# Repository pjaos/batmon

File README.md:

# BATMON

## Overview
The batmon device connects to a Lithium ION battery (primarily aimed at Ebike batteries) and allows the user to
trade off the lifetime of the battery against the maximum single charge. The life of a lithium ION cell
is affected by many things, the maximum charge level of the cell, the temperature of the cell, the maximum
discharge of the cell etc. The batmon device allows the user to limit the maximum charge voltage of the cell
to reduce stresses on the battery chemistry.

For example if the maximum charge voltage of a Lithium ION cell is set to 4.1
volts per cell rather than the maximum of 4.2 volts per cell then the number of charge/discharge cycles
that the battery is capable of could be doubled. The trade off for this is that you will loose about 10 %
of the range on a single charge. If set to 4.0 volts per cell then the number of charge/discharge cycles
that the battery is capable of could be increased by four times. The trade off for this is that you will
loose about 25 % of the range on a single charge. The batmon device allows the user to set this trade off
by selecting the maximum charge voltage in five 0.05 volt steps from 4.2 to 4.0 volts.

The device also ensures that the battery is not charged when to cold or hot which also limits the batteries
lifetime. Charging at temperatures of 0°C or below can also be dangerous.

As stated previously this project is primarily aimed at improving the lifetime of Ebike batteries although the hardware could be used for other battery voltages with slight changes to the software. The device provides a WiFi connection. This can connect to your home WiFi network or run in stand alone (AP) mode. The [Yview App](https://github.com/pjaos/yview/tree/master/gui) can be used (Android phone/tablet or a Windows, Linux PC) to access the state of the battery (charge voltage/current etc) and configure the device settings.

## System Requirements
An initial set of requirements for the system is shown below.

* Charge the battery to a maximum voltage of between 4.0 and 4.2 Volts, configurable by the user.
* Display the charge voltage, current and power.
* Turn off charging if the battery temperature is too cold (<= 0°C).
* Turn off charging if the battery temperature is too hot (> 45°C)g.

## Hardware.
The hardware design uses an ESP32 CPU which provides the WiFi connectivity. An ADS1115 I2C 16 bit ADC device is used to measure the battery voltage, charge current and battery temperature. A Mosfet is used to turn off the battery charge once it reaches the configured charge voltage. The case for the module was 3D printed to provide a robust mount for the module inside the battery case.

")
")

Module installed into case in charger lead.

")

Module installed inside Ebike battery box.

")
")
")

## Software
The software that runs on the device is written in C and uses the [Mongoose OS](https://mongoose-os.com/).
It provides a web interface and integrates with the [YView](https://github.com/pjaos/yview) Iot archetecture.
The web interface is shown below.

The configuration page allow the user to trade off battery charge level against
the longevity of the battery pack via the 5 radio buttons at the top of the page.
 * 5 = max battery life but only charges the battery pack to 4 volts per cell.
 * 1 = min battery life but charges the battery pack to 4.2 volts per cell.

 The default is 3 with charges the battery pack to 4.1 volts per cell. This
 setting should approximately double the life (number of charge discharge cycles) when
 compared option 1. EBike battery chargers will normally charge a battery pack to this level. If option 5 is selected then the life of the battery should be approximately 4 times longer when compared to option 1.

The storage voltage checkbox can be selected if the user wishes to store the ebike for some time (E.G through the winter) and maximise the battery performance. This charges the battery to 3.7 volts.

The Device name can be set which sets the name that the device will appear as in the YView Iot network.

The group name can be set if the user wishes to partition the Iot network such that some users can see some devices.

The Enable syslog option is used for debugging and sends debugging information via the syslog protocol to the server running the YView Iot gateway process.

The save button will apply the configuration selected. The other buttons names are self explanatory.

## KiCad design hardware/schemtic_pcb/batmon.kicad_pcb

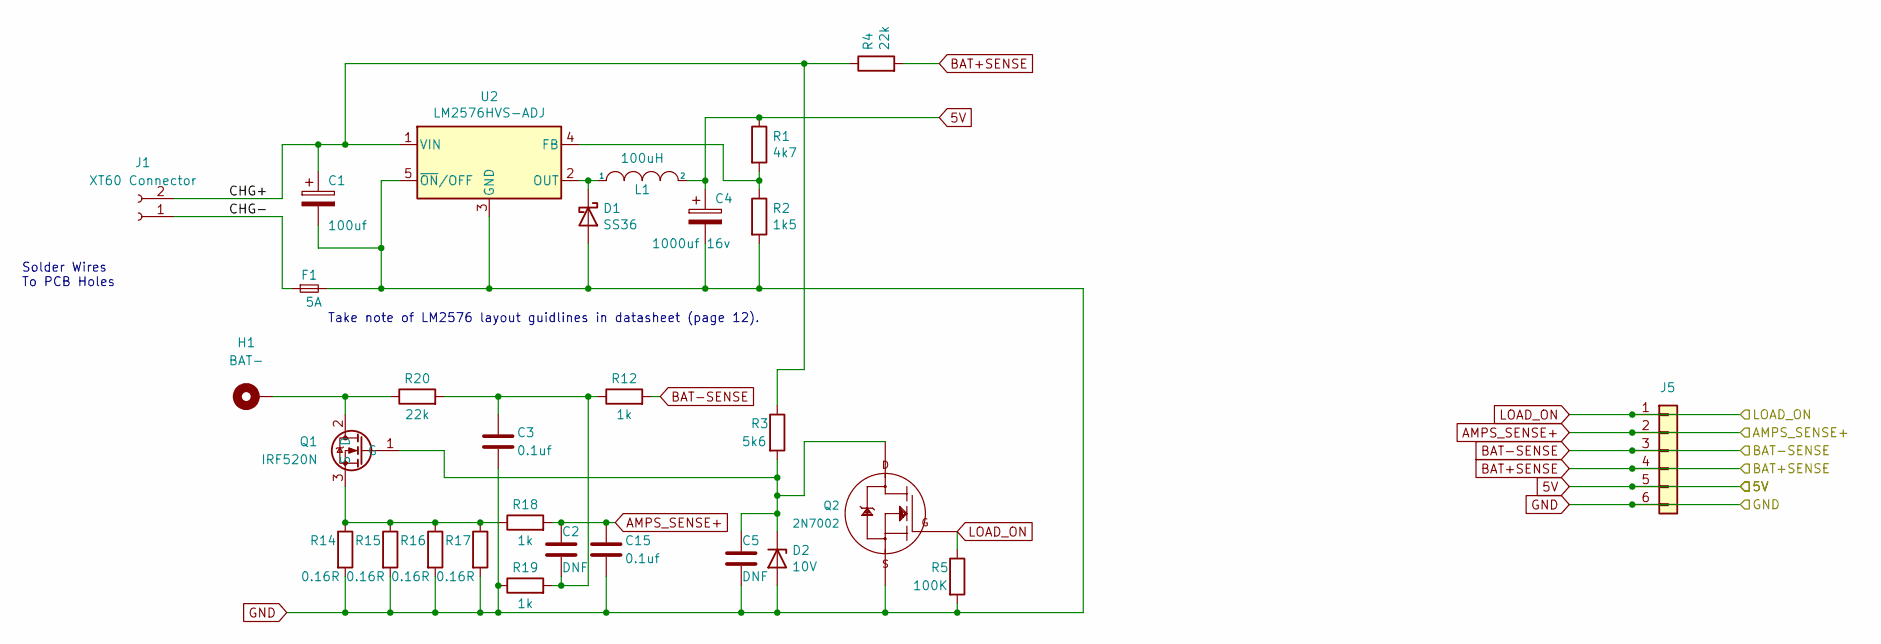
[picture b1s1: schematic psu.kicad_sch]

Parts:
C1: 100uf; CP_Radial_D10.0mm_P5.00mm
C2, C5: DNF; C_0603_1608Metric_Pad1.08x0.95mm_HandSolder
C3, C15: 0.1uf; C_0603_1608Metric_Pad1.08x0.95mm_HandSolder
C4: 1000uf 16v; CP_Radial_D10.0mm_P5.00mm
D1: SS36; D_MELF
D2: 10V; D_MELF
F1: 5A; Scherter_OMT125
H1: BAT-; MountingHole_3.2mm_M3_Pad
J1: XT60 Connector; AMASS_XT60-F_1x02_P7.20mm_Vertical
J5: Conn_01x06; PinHeader_1x06_P2.54mm_Vertical
L1: 100uH; Sumida_CDRH74
Q1: IRF520N; TO-220-3_Vertical
Q2: 2N7002; TSOT-23
R1: 4k7; R_0603_1608Metric_Pad0.98x0.95mm_HandSolder
R2: 1k5; R_0603_1608Metric_Pad0.98x0.95mm_HandSolder
R3: 5k6; R_0603_1608Metric_Pad0.98x0.95mm_HandSolder
R4, R20: 22k; R_0603_1608Metric_Pad0.98x0.95mm_HandSolder
R5: 100K; R_0603_1608Metric_Pad0.98x0.95mm_HandSolder
R12, R18, R19: 1k; R_0603_1608Metric_Pad0.98x0.95mm_HandSolder
R14, R15, R16, R17: 0.16R; R_1206_3216Metric_Pad1.30x1.75mm_HandSolder
U2: LM2576HVS-ADJ; TO-220-5_Vertical

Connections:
5V: C4.1, J5.5, L1.2, R1.1; also elsewhere on the board
/psu/CHG+: C1.1, J1.2, R3.1, R4.1, U2.1 (VIN)
/psu/CHG-: F1.1, J1.1
AMPS_SENSE+: C2.1, C15.1, J5.2, R18.2; also elsewhere on the board
BAT+SENSE: J5.4, R4.2; also elsewhere on the board
BAT-SENSE: J5.3, R12.2; also elsewhere on the board
GND: C1.2, C3.2, C4.2, C5.2, C15.2, D1.2 (A), D2.2 (A), F1.2, J5.6, Q2.2 (S), R2.2, R5.2, R14.2, R15.2, R16.2, R17.2, R19.1, U2.3 (GND), U2.5 (~ON/OFF); also elsewhere on the board
LOAD_ON: J5.1, Q2.1 (G), R5.1; also elsewhere on the board
unnamed: C2.2, C3.1, R12.1, R19.2, R20.2
unnamed: C5.1, D2.1 (K), Q1.1 (G), Q2.3 (D), R3.2
unnamed: D1.1 (K), L1.1, U2.2 (OUT)
unnamed: H1.1, Q1.2 (D), R20.1
unnamed: Q1.3 (S), R14.1, R15.1, R16.1, R17.1, R18.1
unnamed: R1.2, R2.1, U2.4 (FB)

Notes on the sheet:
Take note of LM2576 layout guidlines in datasheet (page 12).
Solder Wires To PCB Holes

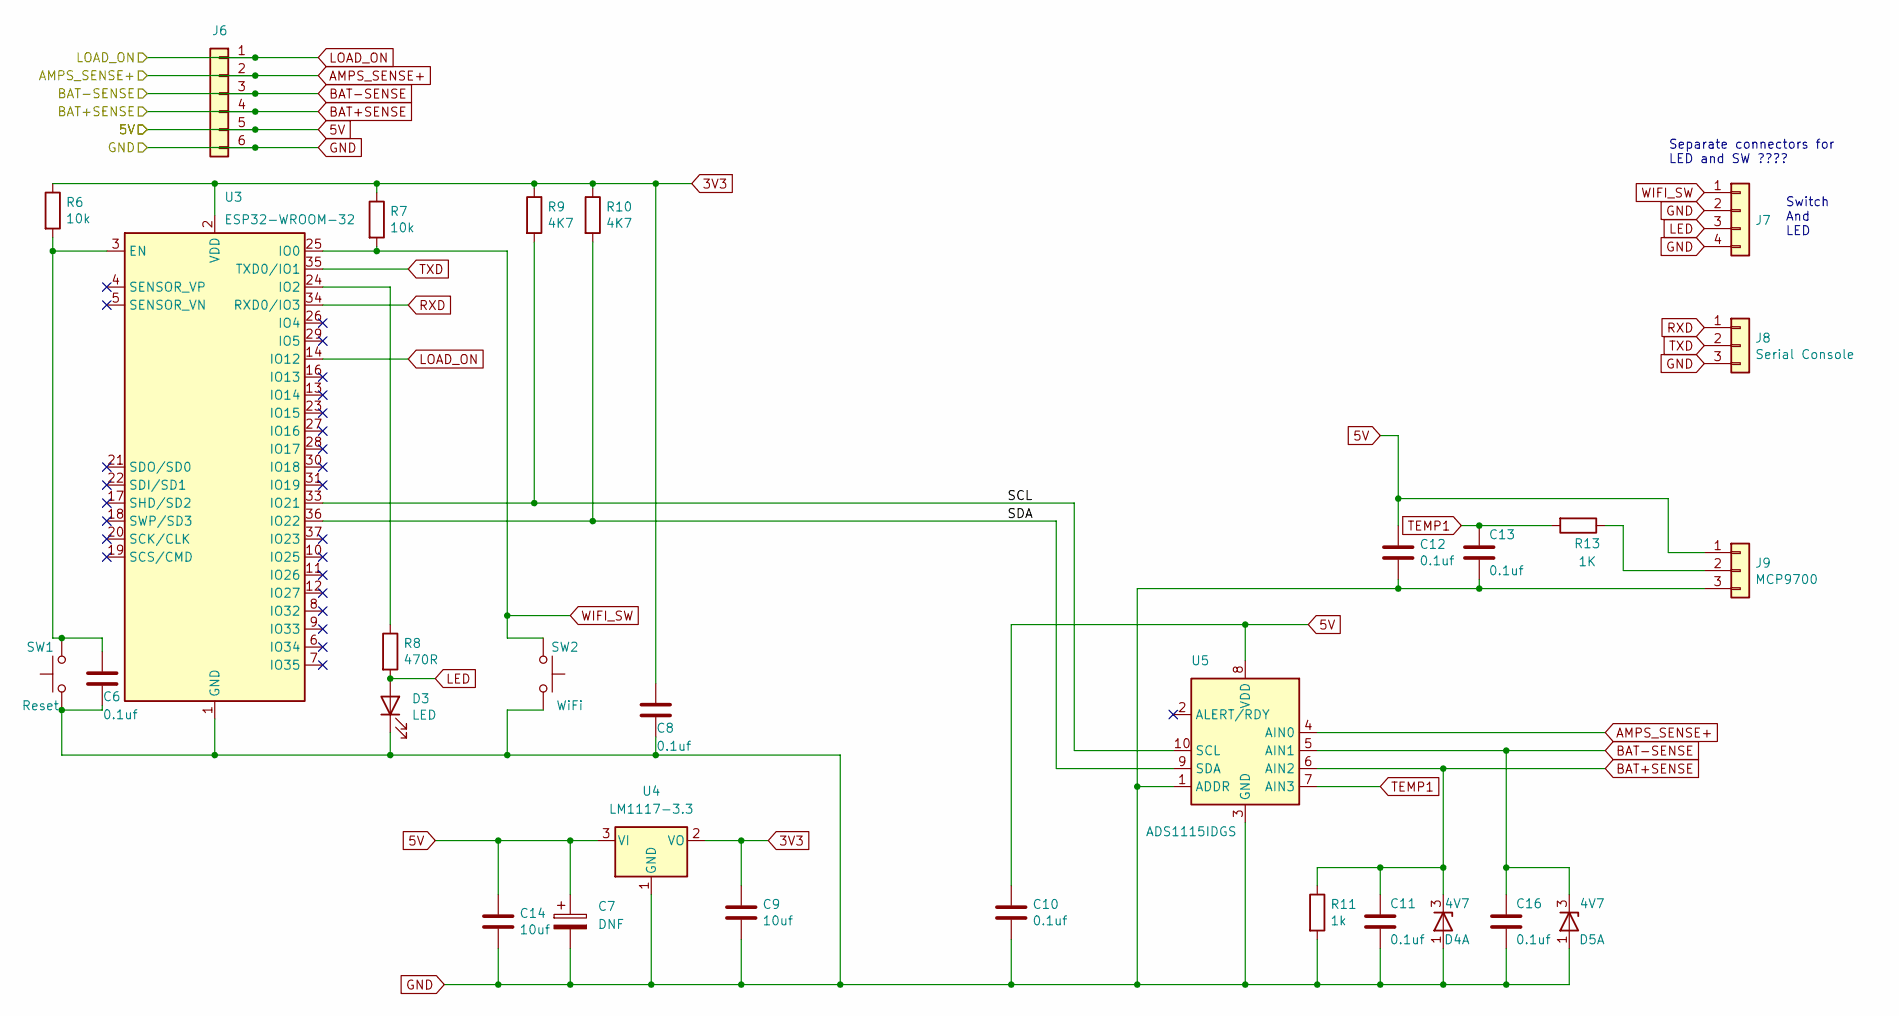
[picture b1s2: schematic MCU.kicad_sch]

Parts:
C6, C8, C10, C11, C12, C13, C16: 0.1uf; C_0603_1608Metric_Pad1.08x0.95mm_HandSolder
C7: DNF; CP_EIA-6032-20_AVX-F_Pad2.25x2.35mm_HandSolder
C9, C14: 10uf; C_1206_3216Metric_Pad1.33x1.80mm_HandSolder
D3: LED; D_1206_3216Metric_Pad1.42x1.75mm_HandSolder
D4, D5: 4V7; SOT-23
J6: Conn_01x06; PinHeader_1x06_P2.54mm_Vertical
J7: SW_&_LED; JST_XH_B4B-XH-A_1x04_P2.50mm_Vertical
J8: Serial Console; JST_XH_B3B-XH-A_1x03_P2.50mm_Vertical
J9: MCP9700; JST_XH_B3B-XH-A_1x03_P2.50mm_Vertical
R6, R7: 10k; R_0603_1608Metric_Pad0.98x0.95mm_HandSolder
R8: 470R; R_0603_1608Metric_Pad0.98x0.95mm_HandSolder
R9, R10: 4K7; R_0603_1608Metric_Pad0.98x0.95mm_HandSolder
R11: 1k; R_0603_1608Metric_Pad0.98x0.95mm_HandSolder
R13: 1K; R_0603_1608Metric_Pad0.98x0.95mm_HandSolder
SW1: Reset; switch_SPST_5mmx3mmx2.5mm
SW2: WiFi; switch_SPST_5mmx3mmx2.5mm
U3: ESP32-WROOM-32
U4: LM1117-3.3; SOT-223-3_TabPin2
U5: ADS1115IDGS; TSSOP-10_3x3mm_P0.5mm

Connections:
3V3: C8.1, C9.1, R6.1, R7.1, R9.1, R10.1, U3.2 (VDD), U4.2 (VO)
5V: C7.1, C10.1, C12.1, C14.1, J6.5, J9.1, U4.3 (VI), U5.8 (VDD); also elsewhere on the board
/MCU/SCL: R9.2, U3.33 (IO21), U5.10 (SCL)
/MCU/SDA: R10.2, U3.36 (IO22), U5.9 (SDA)
AMPS_SENSE+: J6.2, U5.4 (AIN0); also elsewhere on the board
BAT+SENSE: C11.1, D4.3 (K), J6.4, R11.1, U5.6 (AIN2); also elsewhere on the board
BAT-SENSE: C16.1, D5.3 (K), J6.3, U5.5 (AIN1); also elsewhere on the board
GND: C6.2, C7.2, C8.2, C9.2, C10.2, C11.2, C12.2, C13.2, C14.2, C16.2, D3.1 (K), D4.1 (A), D5.1 (A), J6.6, J7.2, J7.4, J8.3, J9.3, R11.2, SW1.1, SW2.1, U3.1 (GND), U3.15 (GND), U3.38 (GND), U3.39 (GND), U4.1 (GND), U5.1 (ADDR), U5.3 (GND); also elsewhere on the board
LED: D3.2 (A), J7.3, R8.2
LOAD_ON: J6.1, U3.14 (IO12); also elsewhere on the board
unnamed: C6.1, R6.2, SW1.2, U3.3 (EN)
unnamed: J9.2, R13.1
unnamed: R8.1, U3.24 (IO2)
RXD: J8.1, U3.34 (RXD0/IO3)
TEMP1: C13.1, R13.2, U5.7 (AIN3)
TXD: J8.2, U3.35 (TXD0/IO1)
WIFI_SW: J7.1, R7.2, SW2.2, U3.25 (IO0)

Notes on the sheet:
Switch And LED
Separate connectors for LED and SW ????

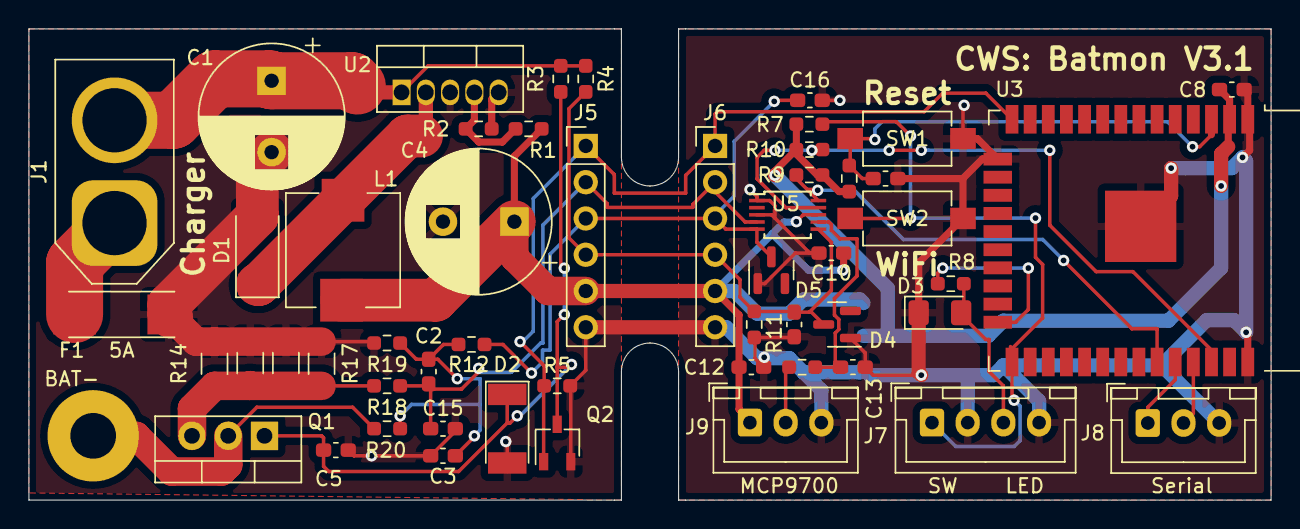
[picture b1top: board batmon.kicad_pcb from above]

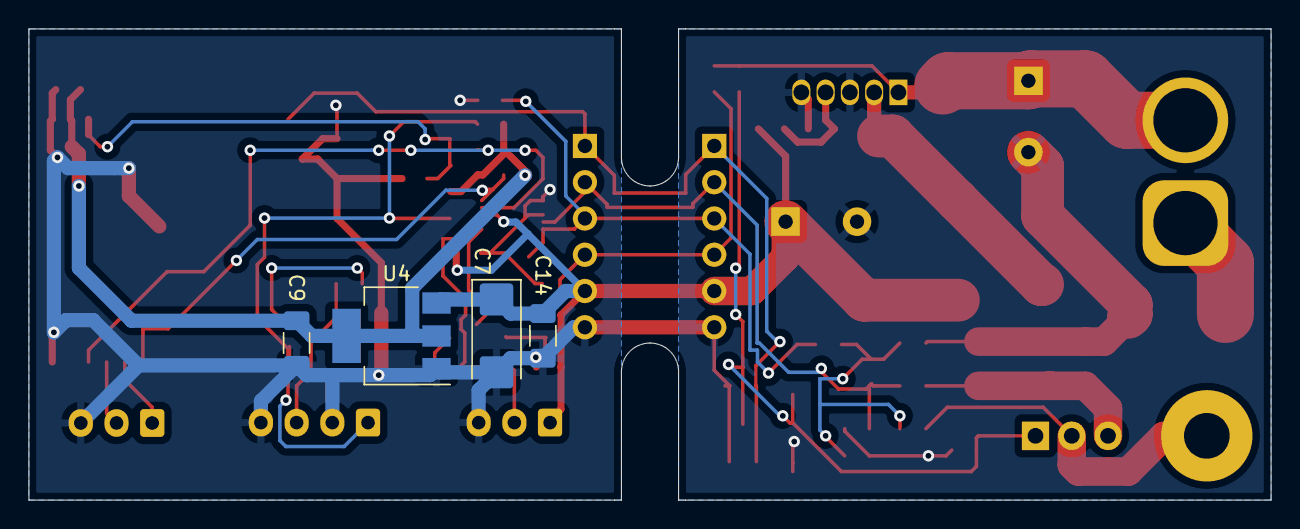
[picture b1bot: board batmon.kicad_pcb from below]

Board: 2 copper layers, 87.0 x 33.0 mm, 58 parts (4 on the bottom side), 25 nets.

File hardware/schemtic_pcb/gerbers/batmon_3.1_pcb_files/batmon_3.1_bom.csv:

Comment,Designator,Footprint,LCSC
"100uf","C1","Capacitor_THT:CP_Radial_D10.0mm_P5.00mm",""
"DNF","C2,C5","Capacitor_SMD:C_0603_1608Metric_Pad1.08x0.95mm_HandSolder",""
"0.1uf","C3,C6,C8,C10,C11,C12,C13,C15,C16","Capacitor_SMD:C_0603_1608Metric_Pad1.08x0.95mm_HandSolder","C14663"
"1000uf 16v","C4","Capacitor_THT:CP_Radial_D10.0mm_P5.00mm",""
"DNF","C7","Capacitor_Tantalum_SMD:CP_EIA-6032-20_AVX-F_Pad2.25x2.35mm_HandSolder",""
"10uf","C9,C14","Capacitor_SMD:C_1206_3216Metric_Pad1.33x1.80mm_HandSolder",""
"SS36","D1","Diode_SMD:D_MELF","C35722"
"10V","D2","Diode_SMD:D_MELF","C50975"
"LED","D3","Diode_SMD:D_1206_3216Metric_Pad1.42x1.75mm_HandSolder",""
"4V7","D4,D5","Package_TO_SOT_SMD:SOT-23","C18206"
"5A","F1","PJA_Fuses:Scherter_OMT125","nn"
"BAT-","H1","MountingHole:MountingHole_3.2mm_M3_Pad",""
"XT60 Connector","J1","Connector_AMASS:AMASS_XT60-F_1x02_P7.20mm_Vertical",""
"Conn_01x06","J5,J6","Connector_PinHeader_2.54mm:PinHeader_1x06_P2.54mm_Vertical",""
"SW_&_LED","J7","Connector_JST:JST_XH_B4B-XH-A_1x04_P2.50mm_Vertical",""
"Serial Console","J8","Connector_JST:JST_XH_B3B-XH-A_1x03_P2.50mm_Vertical",""
"MCP9700","J9","Connector_JST:JST_XH_B3B-XH-A_1x03_P2.50mm_Vertical",""
"100uH","L1","PJA_Inductors:Sumida_CDRH74","C85276"
"IRF520N","Q1","Package_TO_SOT_THT:TO-220-3_Vertical",""
"2N7002","Q2","Package_TO_SOT_SMD:TSOT-23","C8545"
"4k7","R1","Resistor_SMD:R_0603_1608Metric_Pad0.98x0.95mm_HandSolder","C23162"
"1k","R11,R12,R18,R19","Resistor_SMD:R_0603_1608Metric_Pad0.98x0.95mm_HandSolder","C21190"
"1K","R13","Resistor_SMD:R_0603_1608Metric_Pad0.98x0.95mm_HandSolder","C21190"
"0.16R","R14,R15,R16,R17","Resistor_SMD:R_1206_3216Metric_Pad1.30x1.75mm_HandSolder","C175786"
"1k5","R2","Resistor_SMD:R_0603_1608Metric_Pad0.98x0.95mm_HandSolder","C22843"
"5k6","R3","Resistor_SMD:R_0603_1608Metric_Pad0.98x0.95mm_HandSolder","C23189"
"22k","R4,R20","Resistor_SMD:R_0603_1608Metric_Pad0.98x0.95mm_HandSolder","C31850"
"100K","R5","Resistor_SMD:R_0603_1608Metric_Pad0.98x0.95mm_HandSolder","C25803"
"10k","R6,R7","Resistor_SMD:R_0603_1608Metric_Pad0.98x0.95mm_HandSolder","C25804"
"470R","R8","Resistor_SMD:R_0603_1608Metric_Pad0.98x0.95mm_HandSolder","C23179"
"4K7","R9,R10","Resistor_SMD:R_0603_1608Metric_Pad0.98x0.95mm_HandSolder","C23162"
"Reset","SW1","PJA_Switches:switch_SPST_5mmx3mmx2.5mm",""
"WiFi","SW2","PJA_Switches:switch_SPST_5mmx3mmx2.5mm",""
"LM2576HVS-ADJ","U2","Package_TO_SOT_THT:TO-220-5_Vertical",""
"ESP32-WROOM-32","U3","RF_Module:ESP32-WROOM-32",""
"LM1117-3.3","U4","Package_TO_SOT_SMD:SOT-223-3_TabPin2",""
"ADS1115IDGS","U5","Package_SO:TSSOP-10_3x3mm_P0.5mm",""

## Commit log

2022-02-21 Initial commit.
2022-02-21 Rename folder esp32.git to esp32
2022-02-22 Add max cell voltages to config radio buttons.
2022-02-22 Set background color to body to be the same as the header and footer.
2022-02-24 Disable charging if the battery is below 0 °C and display a warning message in the browser window.
2022-02-25 Add details of voltage per cell in the battery voltage tool tip text.
2022-03-11 Add message to show when battery charge is being checked. In the Voltage field report the last voltage on across the battery when it was last charged.
2022-03-11 Set battery charge check period to 1 hour Set charge eveal period to 10 seconds
2022-03-15 Bump schematic and PCB to version 3.0
2022-03-15 Add version 3 of the PCB
2022-03-15 Add 3D printed case.
2022-03-18 Change reboot time to every 5 hours.
2022-03-31 Fix unrouted R12 track that avoided DRC check
2022-04-03 - Update ADC input protextion zenners from 3V9 to 4V7 volts - Fix unrouted track - Update PCB and schemtaic to v3.1
2022-04-03 Add basic requirements for project.
2022-04-03 Add SW support for V3.0 hardware.
2022-04-03 Update TODO with useful features.
2022-04-04 - Set 2 decimal place resolution on amps, volts and watts. - Update default calibration values.
2022-04-04 Update examples with new rpc's
2022-04-15 Add an option to charge the battery to the LION storage voltage.
2022-04-15 - Add missing track (R12)
2022-04-15 - Update schematic notes
2022-04-15 - Return tp 10 cell (36V) battery pack as 7 cells used for testing on a 32 V PSU.
2022-04-21 Remove notes from schematic and pcb.
2022-05-11 Remove some docs from git and update readme doc.
2022-05-11 - Change Charge Voltage to Battery Voltage on web page. - Add smoothed voltage and current values. - Remove commented out debug code.
2022-05-11 git ignore build and deps folders.
2022-05-11 Add a top level readme file.
2022-05-11 Remove some docs from the repo.
2022-05-11 - Ignore some folders and files created by kicad6. - Add pcb archive files.
2022-05-11 Add latest schematic and PCB.
2022-05-11 Add latest case designs.
2022-05-11 Ignore csv and xml kicad output files.
2022-05-11 Update the rest interface command line help.
2022-05-11 Add MIT license for project.
2022-06-22 Update README with details of the SW interface to the module.
2022-06-23 Update README to details the 3D printed case of the device.
2022-06-24 Update readme.
2022-06-24 Save the latest PCB production files of all board versions.
2022-06-24 Save the V3.1 gerber files from Kicad.
2022-06-24 Update git ignore with some of the tmp pcb files.
2022-06-24 rm cache file.
2023-12-21 Add inline box freecad files.
2023-12-21 Add inline case image.
2023-12-21 Add inline case image to project details.
2023-12-22 Set max charge temperature to 60C as now the module may be at ambient temperature if not connected directly to the battery the temperature limit of 45°C was too low.
2023-12-22 Remove file from repo that should not have been present. This was the product.html file while being edited.
2023-12-23 Ignore the freecad backup files.
